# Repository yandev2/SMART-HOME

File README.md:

# Surya Home AI — Asisten Smart Home Dinamis

Asisten Smart Home berbasis Web yang bisa diajak ngobrol santai, ceria, dan bercanda menggunakan **Gemini API (`@google/genai`)**, dengan kontrol perangkat dinamis via **Supabase** dan **NodeMCU ESP8266**.

## Fitur Utama
- **Asisten AI Santai & Ceria (`gemini-4-hydrogen`)**: Bisa membedakan obrolan santai dengan perintah menyalakan, mematikan, atau mengecek kondisi perangkat rumah (via *Interactions API & Function Calling*).
- **Manajemen Ruangan & Perangkat Dinamis**: Tambah, ubah nama, dan hapus ruangan serta perangkat langsung lewat form menu di Web Dashboard — AI langsung mengenali perubahan tanpa ubah kode.
- **Fleksibel 1 atau Banyak Relay per NodeMCU**: 1 unit NodeMCU bisa mengontrol 1 relay maupun banyak relay sekaligus melalui pemetaan pin GPIO di Web, dengan satu sketch firmware yang sama.
- **Realtime Dashboard**: Status perangkat ter-update otomatis menggunakan Supabase Realtime.

---

## Cara Setup

### 1. Siapkan Database Supabase
1. Buat project gratis di [Supabase](https://supabase.com).
2. Buka **SQL Editor** di Dashboard Supabase, lalu jalankan isi file `supabase/schema.sql`.
3. (Opsional untuk testing cepat) Di **Authentication -> Providers -> Email**, kamu bisa mematikan *Confirm email* agar akun baru bisa langsung login tanpa verifikasi email.

### 2. Konfigurasi Environment Variable
Salin `.env.example` menjadi `.env.local` lalu isi nilainya:

```env
NEXT_PUBLIC_SUPABASE_URL=https://xxxxx.supabase.co
NEXT_PUBLIC_SUPABASE_ANON_KEY=eyJ...
SUPABASE_SERVICE_ROLE_KEY=eyJ...
APP_ENCRYPTION_KEY=string-acak-minimal-32-karakter
```

- Kunci Supabase ada di **Project Settings -> API**.
- `APP_ENCRYPTION_KEY` digunakan untuk mengenkripsi Gemini API Key tiap user di database Supabase (jika dikosongkan, sistem otomatis menurunkannya dari `SUPABASE_SERVICE_ROLE_KEY`).
- **Gemini API Key** tidak disimpan di `.env`: setiap user cukup login lalu memasukkan API Key miliknya sendiri (dari [Google AI Studio](https://aistudio.google.com/apikey)) melalui tab **API Key** di Web Dashboard.

### 3. Jalankan Aplikasi Web
```bash
npm install
npm run dev
```
Buka `http://localhost:3000`, daftar akun, lalu tambahkan **Ruangan**, **NodeMCU**, dan **Perangkat**.

### 4. Upload Firmware ke NodeMCU (ESP8266)
1. Buka `firmware/nodemcu_smart_home/nodemcu_smart_home.ino` di Arduino IDE.
2. Install board **esp8266** (`NodeMCU 1.0 (ESP-12E Module)`) melalui Boards Manager. Tidak perlu install library eksternal tambahan.
3. (Opsional) Sesuaikan `DEFAULT_SYNC_URL` ke URL server web kamu (misal URL Vercel atau `http://<IP-LAN-PC>:3000/api/iot/sync`) — bisa juga diisi nanti lewat Portal Web NodeMCU.
4. Upload ke NodeMCU. Setelah flash pertama, NodeMCU otomatis memancarkan Access Point **`SmartHome-Setup-XXXX`** (buka `http://192.168.4.1`) untuk mengisi **Nama Wi-Fi**, **Password Wi-Fi**, dan **Device Token** dari menu **NodeMCU** di Web Dashboard.
5. Jika suatu saat Wi-Fi gagal terhubung, password salah, atau terputus melewati batas timeout, NodeMCU otomatis kembali masuk ke mode Access Point agar kamu bisa mengatur ulang Wi-Fi dan Token.

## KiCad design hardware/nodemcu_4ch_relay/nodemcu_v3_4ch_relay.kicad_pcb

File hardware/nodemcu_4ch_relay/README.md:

# Desain PCB Smart Switch — NodeMCU V3 LoLin + 4-Channel Relay (Single-Layer / Komponen Besar)

Paket desain PCB **1-Layer (`B.Cu` / Bottom Copper ONLY, `149 mm × 116 mm`)** dengan ukuran komponen **through-hole standar besar (gaya amplifier/audio)** siap cetak rumahan (sablon/setrika FeCl3, CNC) maupun pabrik, dan siap di-import langsung ke **EasyEDA** untuk **NodeMCU V3 LoLin (`30 pin`, lebar baris `27.94 mm / 1.1"`)**, **4× Relay 5V (`SRD-05VDC-SL-C`)**, **Terminal 4× Push Button Manual (`J6` — kontrol offline & sinkron dua arah)**, serta suplai **5V DC dari adaptor charger HP**.

---

## 1. File di Folder Ini
- **[nodemcu_v3_4ch_relay_easyeda.zip](nodemcu_v3_4ch_relay_easyeda.zip)** → File utama untuk di-import ke EasyEDA.
- **[nodemcu_v3_4ch_relay.kicad_pcb](nodemcu_v3_4ch_relay.kicad_pcb)** → Source PCB format KiCad v5 (`version 20171130`), **100% Single-Layer (`0` jalur di `F.Cu`, `197` jalur di `B.Cu`)**, `62` modul, `175` pad, `54` net, plus copper pour `GND` di sisi kiri DC.

---

## 2. Keunggulan Desain Single-Layer & Komponen Standar Besar
- **100% Jalur di Bottom (`B.Cu` ONLY)**: Nol jalur tembaga di Top layer (`F.Cu`), cocok untuk etsa PCB polos 1-sisi maupun cetak single-layer di vendor PCB.
- **Kaki Komponen Besar (Non-Micro)**:
  - **Resistor `1/4W` – `1/2W`**: jarak kaki **`10.16 mm` (`0.4"`)**, pad `2.2 × 2.2 mm` (lubang `0.9 mm`).
  - **Dioda `1N4007` / `1N5819` (`DO-41`)**: jarak kaki **`10.16 mm`**, pad `2.4 × 2.4 mm` (lubang `1.0 mm`).
  - **Elco `1000µF / 16V`**: diameter `10 mm`, jarak kaki **`5.0 mm`**, pad `2.6 × 2.6 mm`.
  - **Kapasitor MKT / Keramik `100nF`**: jarak kaki **`5.0 mm`**, pad `2.2 × 2.2 mm`.
  - **Transistor `S8050` / `BC547` (`TO-92`)**: kaki diluruskan melebar ke pitch **`2.54 mm`**, pad `2.0 × 1.8 mm`.
  - **Fuse `PTC 1A`**: jarak kaki **`7.62 mm`**, pad `2.4 × 2.4 mm`.
- **Jalur Lebar & Aman**: Sinyal `0.6–0.8 mm`, Power DC `1.0–1.5 mm`, Jalur AC 220V **`2.8 mm`**, celah isolasi AC–DC minimal **`3.30 mm`**, dan bebas copper pour di zona AC kanan.

---

## 3. Cara Import ke EasyEDA & Generate File Cetak (Gerber)
1. Buka **[EasyEDA Standard](https://easyeda.com/editor)** di browser dan login.
2. Klik menu **File → Import → KiCad...**
3. Pilih file **`nodemcu_v3_4ch_relay_easyeda.zip`** *(EasyEDA mewajibkan file `.kicad_pcb` dibungkus di dalam `.zip`)*.
4. Setelah terbuka:
   - Pastikan **Copper Area (`GND`)** di Bottom layer aktif, lalu tekan **Shift + B** (*Rebuild All Copper Areas*) agar area ground terisi penuh.
   - Jalankan **Design → Check DRC** untuk verifikasi final di EasyEDA.
   - Klik **Fabrication → PCB Fabrication File (Gerber)** (atau export ke PDF / Mirror `BottomLayer` untuk cetak setrika/sablon DIY).

---

## 4. Pemetaan Pin NodeMCU V3 LoLin ↔ Relay & Web Dashboard

> **Orientasi Pemasangan `U1` (NodeMCU V3 LoLin)**: Antena PCB menghadap ke **ATAS**, port Micro-USB menghadap ke **BAWAH**.

| Channel | Pin Relay | GPIO Relay | Pin Push Button (`J6`) | Driver | Relay & Terminal | Setting di Web Dashboard |
| :---: | :---: | :---: | :---: | :--- | :--- | :--- |
| **CH 1** | `D1` (Pin 4) | `GPIO 5` | `D7 (GPIO 13)` → `J6 Pin 2` | `U2 (PC817)` + `Q1 (S8050)` | `K1` → `J2 (NC, COM, NO)` | Pin `D1 (GPIO 5)`, `Active LOW = Aktif` |
| **CH 2** | `D2` (Pin 5) | `GPIO 4` | `D4 (GPIO 2)` → `J6 Pin 3` | `U3 (PC817)` + `Q2 (S8050)` | `K2` → `J3 (NC, COM, NO)` | Pin `D2 (GPIO 4)`, `Active LOW = Aktif` |
| **CH 3** | `D5` (Pin 10) | `GPIO 14` | `D3 (GPIO 0)` → `J6 Pin 4` | `U4 (PC817)` + `Q3 (S8050)` | `K3` → `J4 (NC, COM, NO)` | Pin `D5 (GPIO 14)`, `Active LOW = Aktif` |
| **CH 4** | `D6` (Pin 11) | `GPIO 12` | `D0 (GPIO 16)` → `J6 Pin 5` | `U5 (PC817)` + `Q4 (S8050)` | `K4` → `J5 (NC, COM, NO)` | Pin `D6 (GPIO 12)`, `Active LOW = Aktif` |

> **Wiring Terminal Push Button (`J6` — 5-Pin `P5.08mm` di kiri bawah PCB)**:
> - `J6 Pin 1` = **`GND`** *(kabel ground bersama untuk semua 4 tombol)*
> - `J6 Pin 2` = **`BTN 1`** (terhubung ke saklar momentary/push button 1 ↔ `GND`)
> - `J6 Pin 3` = **`BTN 2`** (terhubung ke saklar momentary/push button 2 ↔ `GND`)
> - `J6 Pin 4` = **`BTN 3`** (terhubung ke saklar momentary/push button 3 ↔ `GND`)
> - `J6 Pin 5` = **`BTN 4`** (terhubung ke saklar momentary/push button 4 ↔ `GND`)
> - Gunakan saklar tipe **Push Button / Momentary (Bell Switch)**, **1× tekan = ON, 1× tekan = OFF**. Jangan sambungkan listrik 220V AC ke `J6`!
> - Ke-4 tombol tetap bekerja normal saat **Wi-Fi mati**, dan otomatis tersinkron ke Web/AI begitu Wi-Fi pulih. Tahan **`BTN 1 + BTN 2` selama 5 detik** untuk masuk Mode Portal Setup Wi-Fi kapan saja.

---

## 5. Daftar Kawat Jumper Sisi Atas (`JMP1–JMP7`)
Karena menggunakan 1-layer murni, terdapat **7 kawat jumper lurus horizontal** di sisi atas komponen (pakai potongan kaki resistor/dioda atau resistor `0Ω`) agar jalur tanpa persilangan dan EasyEDA DRC bersih:

| Ref | Pitch | Keterangan Jalur |
| :--- | :---: | :--- |
| `JMP1` | `17.78 mm` | Jembatan sinyal `GPIO 4 (D2 → CH2)` melompati jalur `5V_SYS`, `3V3`, dan `GPIO5_R` |
| `JMP2` | `15.24 mm` | Jembatan sinyal `GPIO 5 (D1 → CH1)` melompati jalur `5V_SYS` dan `3V3` |
| `JMP3` | `10.16 mm` | Jembatan sinyal `GPIO 12 (D6 → CH4)` melompati jalur `GND` |
| `JMP4` | `16.51 mm` | Jembatan sinyal `GPIO 14 (D5 → CH3)` melompati jalur `GND` dan `GPIO12_R` |
| `JMP5` | `10.16 mm` | Jembatan suplai `+5V` ke koil & flyback **CH 2 (`K2`)** melompati tulang `GND` |
| `JMP6` | `10.16 mm` | Jembatan suplai `+5V` ke koil & flyback **CH 3 (`K3`)** melompati tulang `GND` |
| `JMP7` | `10.16 mm` | Jembatan suplai `+5V` ke koil & flyback **CH 4 (`K4`)** melompati tulang `GND` |

*(Catatan: Untuk mempermudah solder `JMP1–JMP4` yang berada di atas/bawah area NodeMCU, disarankan memasang `U1` memakai soket **Pin Header Female `1×15`**, lalu jumper disolder rata PCB sebelum NodeMCU ditancapkan.)*

---

## 6. Daftar Komponen (BOM — Ukuran Standar Besar)

| Ref | Komponen & Nilai | Ukuran / Pitch | Qty | Catatan |
| :--- | :--- | :---: | :---: | :--- |
| `U1` | Pin Header Female `1×15 Pin` × 2 | `2.54 mm` (antar baris `27.94 mm`) | 2 | Soket **NodeMCU V3 LoLin** |
| `J1` | Screw Terminal `2-Pin` (KF301) | `5.08 mm` | 1 | Input `5V DC` charger HP (`Pin 1 = GND [bulat]`, `Pin 2 = +5V [kotak]`) |
| `F1` | Resettable Fuse `PTC 1A` / Fuse | `7.62 mm` | 1 | Pengaman arus lebih jalur 5V |
| `D1` | Dioda `1N5819` atau `1N4007` (`DO-41`) | `10.16 mm` | 1 | Pengaman polaritas terbalik (`1=Katoda [kotak]`, `2=Anoda`) |
| `C1` | Elco `1000µF / 16V` | `Ø10 mm, P 5.0 mm` | 1 | Menahan lonjakan arus saat 4 relay aktif bersamaan (`1=+ [kotak]`, `2=-`) |
| `C2` | Kapasitor MKT / Keramik `100nF (104)` | `P 5.0 mm` | 1 | Filter noise jalur 5V |
| `J6` | Screw Terminal `5-Pin` (KF301/MKDS) | `P 5.08 mm` | 1 | Terminal 4× Push Button (`1=GND`, `2=BTN1`, `3=BTN2`, `4=BTN3`, `5=BTN4`) |
| `R13–R16` | Resistor `1kΩ` 1/4W–1/2W (dipasang tegak / bridge) | `P 12.2 mm` | 4 | Proteksi ESD & jembatan sinyal `BTN1–BTN4` dari bawah NodeMCU ke `J6` |
| `R17–R20` | Resistor `4.7kΩ` 1/4W–1/2W | `P 10.16 mm` | 4 | Pull-up eksternal ke `3V3` di bawah area `U1` (wajib agar `D0/D3/D4/D7` stabil `HIGH` saat boot) |
| `C3–C6` | Kapasitor MKT / Keramik `100nF (104)` | `P 5.0 mm` | 4 | Filter anti-bounce & peredam interferensi kabel saklar dinding ke `GND` |
| `U2–U5` | Optocoupler `PC817` (`DIP-4`) | `7.62 × 2.54 mm` | 4 | Isolasi `3.3V` NodeMCU dari driver `5V` |
| `Q1–Q4` | Transistor NPN `S8050` / `BC547` (`TO-92`) | `P 2.54 mm` inline | 4 | **Cek pinout**: susunan kaki pada PCB `Pin 1 = E (bawah/GND)`, `Pin 2 = B (tengah)`, `Pin 3 = C (atas/Koil-)` *(cocok langsung untuk `S8050` sisi datar menghadap kanan; jika pakai `2N2222`/`BC547`, sesuaikan kaki E-B-C saat menekuk!)* |
| `D2–D5` | Dioda Flyback `1N4007` (`DO-41`) | `10.16 mm` | 4 | Dipasang paralel terbalik pada koil relay (`1=Katoda [+5V]`, `2=Anoda [Koil-]`) |
| `R1, R4, R7, R10` | Resistor `330Ω` 1/4W–1/2W | `10.16 mm` | 4 | Pembatas arus LED PC817 |
| `R2, R5, R8, R11` | Resistor `1kΩ` 1/4W–1/2W | `10.16 mm` | 4 | Resistor basis transistor `Q1–Q4` |
| `R3, R6, R9, R12` | Resistor `10kΩ` 1/4W–1/2W | `10.16 mm` | 4 | Pull-down basis `Q1–Q4` |
| `K1–K4` | Relay 5V 10A SPDT (`SRD-05VDC-SL-C`) | Standar Songle | 4 | Beban AC 220V terpisah di sisi kanan PCB |
| `J2–J5` | Screw Terminal `3-Pin` (KF301) | `5.08 mm` | 4 | Output AC 220V (`1=NC [atas]`, `2=COM [tengah]`, `3=NO [bawah]`) |
| `JMP1–JMP7` | Kawat Jumper / Resistor `0Ω` | `10.16 – 17.78 mm` | 7 | Disolder di sisi atas PCB |
| `H1–H4` | Lubang Baut `M3` | `Ø3.2 mm` | 4 | Di keempat sudut PCB |

---

## 7. Catatan Penting Catu Daya & Keselamatan
- **Gunakan terminal `J1` untuk sumber 5V Charger HP** (minimal `5V 2A`), bukan mencolokkan beban 4 koil relay lewat port USB NodeMCU, agar dioda proteksi USB pada NodeMCU V3 tidak kelebihan beban.
- Saat **upload firmware** via kabel USB ke NodeMCU, cabut dulu suplai eksternal `5V` di `J1` (atau cabut NodeMCU dari soketnya).
- Pastikan pemasangan **`Q1–Q4` (`E-B-C`)** dan polaritas **`D1–D5`, `C1`, `U2–U5`** sesuai tanda pad kotak/silkscreen sebelum menyalakan daya.

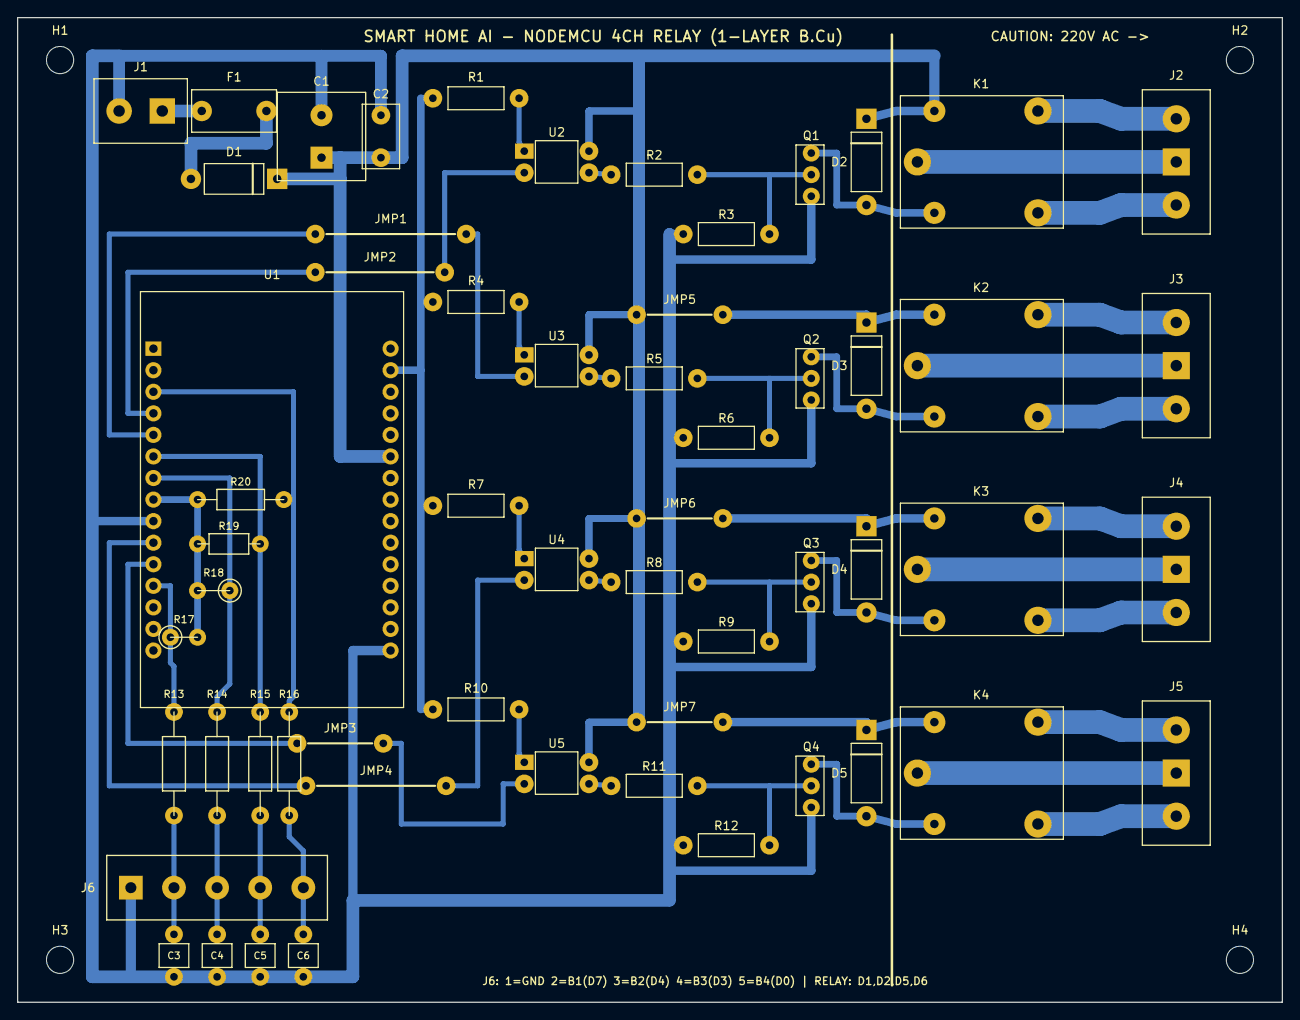
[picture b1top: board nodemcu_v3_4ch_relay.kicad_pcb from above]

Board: 2 copper layers, 149.0 x 116.0 mm, 62 parts (0 on the bottom side), 53 nets.

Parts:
C1: 1000uF_16V; CP_Radial_D10.0mm_P5.00mm
C2, C3, C4, C5, C6: 100nF; C_Rect_L7.2mm_W3.5mm_P5.00mm
D1: 1N5819; D_DO-41_SOD81_P10.16mm_Horizontal
D2, D3, D4, D5: 1N4007; D_DO-41_SOD81_P10.16mm_Vertical
F1: PTC_1A; Fuse_Radial_D7.2mm_P7.62mm
H1, H2, H3, H4: M3; MountingHole_3.2mm_M3
J1: 5V_CHARGER_IN; TerminalBlock_Phoenix_MKDS-1,5-2-5.08_1x02_P5.08mm_Horizont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
J2: AC_CH1; TerminalBlock_Phoenix_MKDS-1,5-3-5.08_1x03_P5.08mm_Horizont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
J3: AC_CH2; TerminalBlock_Phoenix_MKDS-1,5-3-5.08_1x03_P5.08mm_Horizont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
J4: AC_CH3; TerminalBlock_Phoenix_MKDS-1,5-3-5.08_1x03_P5.08mm_Horizont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
J5: AC_CH4; TerminalBlock_Phoenix_MKDS-1,5-3-5.08_1x03_P5.08mm_Horizont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
J6: PUSH_BTN_5P; TerminalBlock_Phoenix_MKDS-1,5-5-5.08_1x05_P5.08mm_Horizont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
JMP1: JUMPER_0R; Jumper_2_Open_P17.78mm_Horizontal
JMP2: JUMPER_0R; Jumper_2_Open_P15.24mm_Horizontal
JMP3, JMP5, JMP6, JMP7: JUMPER_0R; Jumper_2_Open_P10.16mm_Horizontal
JMP4: JUMPER_0R; Jumper_2_Open_P16.51mm_Horizontal
K1, K2, K3, K4: SRD-05VDC-SL-C; Relay_SPDT_SANYOU_SRD_Series_Form_C
Q1, Q2, Q3, Q4: S8050; TO-92_Inline_Wide_P2.54mm
R1, R4, R7, R10: 330R; R_Axial_DIN0207_L6.3mm_D2.5mm_P10.16mm_Horizontal
R2, R5, R8, R11: 1k; R_Axial_DIN0207_L6.3mm_D2.5mm_P10.16mm_Horizontal
R3, R6, R9, R12: 10k; R_Axial_DIN0207_L6.3mm_D2.5mm_P10.16mm_Horizontal
R13, R14, R15, R16: 1k; R_Axial_DIN0207_L6.3mm_D2.5mm_P12.2mm_VerticalBridge
R17, R18: 4k7; R_Axial_DIN0207_Standing_Upright
R19, R20: 4k7; R_Axial_DIN0207_L6.3mm_D2.5mm_Horizontal
U1: NodeMCU_V3_LoLin; NodeMCU_V3_LoLin_30Pin
U2, U3, U4, U5: PC817; DIP-4_W7.62mm

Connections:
3V3: R1.1, R4.1, R7.1, R10.1, U1.29
3V3_BTN: R17.2, R18.1, R19.1, R20.1, U1.8
5V_FUSED: D1.2, F1.2
5V_RAW: F1.1, J1.2
5V_SYS: C1.1, C2.1, D1.1, D2.1, JMP5.1, JMP6.1, JMP7.1, K1.5, U1.25, U2.4, U3.4, U4.4, U5.4
AC_CH1_COM: J2.2, K1.1
AC_CH1_NC: J2.1, K1.4
AC_CH1_NO: J2.3, K1.3
AC_CH2_COM: J3.2, K2.1
AC_CH2_NC: J3.1, K2.4
AC_CH2_NO: J3.3, K2.3
AC_CH3_COM: J4.2, K3.1
AC_CH3_NC: J4.1, K3.4
AC_CH3_NO: J4.3, K3.3
AC_CH4_COM: J5.2, K4.1
AC_CH4_NC: J5.1, K4.4
AC_CH4_NO: J5.3, K4.3
BTN1_EXT: C3.1, J6.2, R13.2
BTN2_EXT: C4.1, J6.3, R14.2
BTN3_EXT: C5.1, J6.4, R15.2
BTN4_EXT: C6.1, J6.5, R16.2
CH1_BASE: Q1.2, R2.2, R3.2
CH1_COIL_M: D2.2, K1.2, Q1.3
CH1_OPTO_A: R1.2, U2.1
CH1_OPTO_E: R2.1, U2.3
CH2_5V_BR: D3.1, JMP5.2, K2.5
CH2_BASE: Q2.2, R5.2, R6.2
CH2_COIL_M: D3.2, K2.2, Q2.3
CH2_OPTO_A: R4.2, U3.1
CH2_OPTO_E: R5.1, U3.3
CH3_5V_BR: D4.1, JMP6.2, K3.5
CH3_BASE: Q3.2, R8.2, R9.2
CH3_COIL_M: D4.2, K3.2, Q3.3
CH3_OPTO_A: R7.2, U4.1
CH3_OPTO_E: R8.1, U4.3
CH4_5V_BR: D5.1, JMP7.2, K4.5
CH4_BASE: Q4.2, R11.2, R12.2
CH4_COIL_M: D5.2, K4.2, Q4.3
CH4_OPTO_A: R10.2, U5.1
CH4_OPTO_E: R11.1, U5.3
GND: C1.2, C2.2, C3.2, C4.2, C5.2, C6.2, J1.1, J6.1, Q1.1, Q2.1, Q3.1, Q4.1, R3.1, R6.1, R9.1, R12.1, U1.9, U1.16
GPIO0_BTN3: R15.1, R19.2, U1.6
GPIO2_BTN2: R14.1, R18.2, U1.7
GPIO4_CH2: JMP1.1, U1.5
GPIO4_R: JMP1.2, U3.2
GPIO5_CH1: JMP2.1, U1.4
GPIO5_R: JMP2.2, U2.2
GPIO12_CH4: JMP3.1, U1.11
GPIO12_R: JMP3.2, U5.2
GPIO13_BTN1: R13.1, R17.1, U1.12
GPIO14_CH3: JMP4.1, U1.10
GPIO14_R: JMP4.2, U4.2
GPIO16_BTN4: R16.1, R20.2, U1.3
